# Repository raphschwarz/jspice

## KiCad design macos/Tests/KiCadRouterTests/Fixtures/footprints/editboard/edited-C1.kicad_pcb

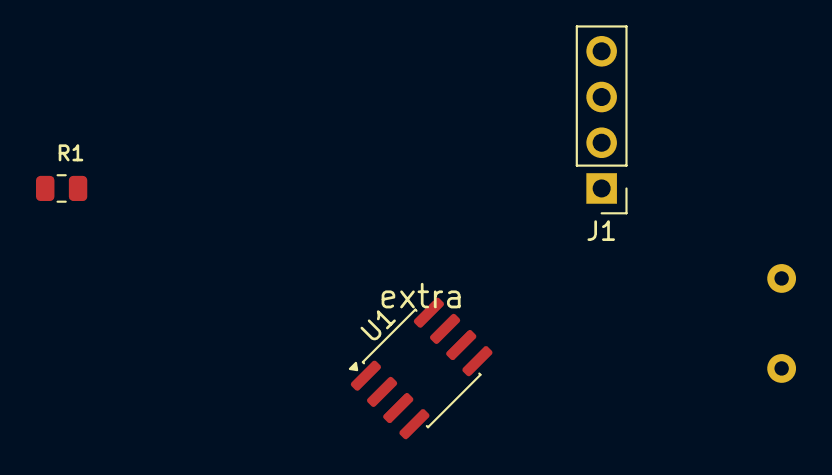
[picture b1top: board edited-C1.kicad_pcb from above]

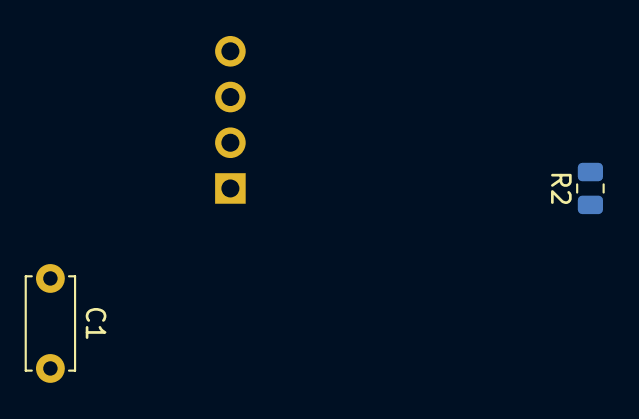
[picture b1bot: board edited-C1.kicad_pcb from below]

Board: 2 copper layers, 5 parts (2 on the bottom side), 2 nets, no tracks yet.

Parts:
C1: 100n; C_Disc_D5.0mm_W2.5mm_P5.00mm
J1: Conn_01x04; PinHeader_1x04_P2.54mm_Vertical
R1: 10k; R_0805_2012Metric
R2: R_0805_2012Metric
U1: LM358; SOIC-8_3.9x4.9mm_P1.27mm

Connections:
GND: R1.1, U1.2
VCC: R1.2 (B), U1.3
